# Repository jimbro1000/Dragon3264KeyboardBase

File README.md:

# Reproduction Keyboard for Dragon 32 and 64 #

This project provides the design for a reproduction keyboard
to fit the Dragon 32 and 64 home computers. The design here is
a complement to the main keyboard PCB. This provides mounting
points to the case and additional wiring to convert the board
to the CoCo connector

The conversion works by letting the top board plugin vertically
while letting the CoCo connector plugin underneath horizontally

## Future Plans ##

To further increase functionality the plan is to add support to
make the keyboard HID compliant by the addition of a cheap 
microcontroller board such as an arduino or a pico

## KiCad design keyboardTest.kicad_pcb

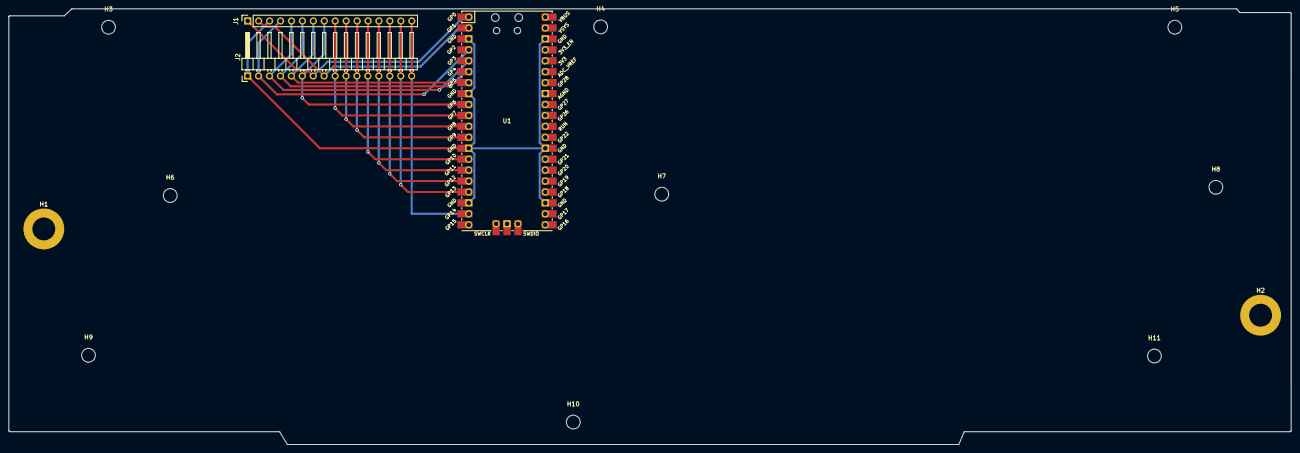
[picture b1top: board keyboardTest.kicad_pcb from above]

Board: 2 copper layers, 297.8 x 101.2 mm, 14 parts (0 on the bottom side), 16 nets.

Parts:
H1, H2: MountingHole; MountingHole_5.3mm_M5_ISO7380_Pad
H3, H4, H5, H6, H7, H8, H9, H10, H11: MountingHole; MountingHole_3.2mm_M3
J1: DRAGON_CONNECTION; PinSocket_1x16_P2.54mm_Vertical
J2: COCO_CONNECTION; PinHeader_1x16_P2.54mm_Horizontal
U1: Pico; RPi_Pico_SMD_TH

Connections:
GND: J1.3, J2.1, U1.3 (GND), U1.8 (GND), U1.13 (GND), U1.18 (GND), U1.23 (GND), U1.28 (GND), U1.38 (GND)
PA0: J1.1, J2.7, U1.1 (GPIO0)
PA1: J1.2, J2.8, U1.2 (GPIO1)
PA2: J1.4, J2.2, U1.4 (GPIO2)
PA3: J1.5, J2.3, U1.5 (GPIO3)
PA4: J1.6, J2.4, U1.6 (GPIO4)
PA5: J1.7, J2.5, U1.7 (GPIO5)
PA6: J1.8, J2.6, U1.9 (GPIO6)
PB0: J1.9, J2.9, U1.10 (GPIO7)
PB1: J1.10, J2.10, U1.11 (GPIO8)
PB2: J1.11, J2.11, U1.12 (GPIO9)
PB3: J1.12, J2.12, U1.14 (GPIO10)
PB4: J1.13, J2.13, U1.15 (GPIO11)
PB5: J1.14, J2.14, U1.16 (GPIO12)
PB6: J1.15, J2.15, U1.17 (GPIO13)
PB7: J1.16, J2.16, U1.19 (GPIO14)

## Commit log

2023-08-08 add pico for hid
2023-08-23 update board mounting
2023-08-25 reshape board for fit
